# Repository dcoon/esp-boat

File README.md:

# ESP32 Multitool

ESP32 Multitool is an I/O board for ESP32 microcontroller based projects.  It is designed for IoT projects on a boat but can be used in automotive, RV, and home environments.  It is designed to be inexpensive, robust, energy efficient, and easy to use.  It supports firmware from multiple open source projects including ESPHome, ESPSense, and Platformio.

![[esp32-multitool.png]]

## Features

- 4x Analog Inputs
	- +0-30VDC
	- Measure voltage or resistance
- 4x Digital Inputs
- 4x PWM/Switch Outputs
	- Configurable voltage from VIN, +5V, and External
	- 1A current per channel
- CAN/N2K 
- 1-Wire
- I2C
	- Qwiic and Adafruit compatible I2C connector
- Power
	- +5 - 30VDC Input
	- OVP, RV, and ESD Protection
- Software Compatibility
	- ESPHome
	- ESPSense
	- Platformio

## Examples

TBD

### Tank Level Monitor
### Engine Monitor
### Fan Controller
### LED Dimmer

### More
- Refridgerator Controller
- Barometer & Lightning Detector

## Acknowledgements

### Sailorhat

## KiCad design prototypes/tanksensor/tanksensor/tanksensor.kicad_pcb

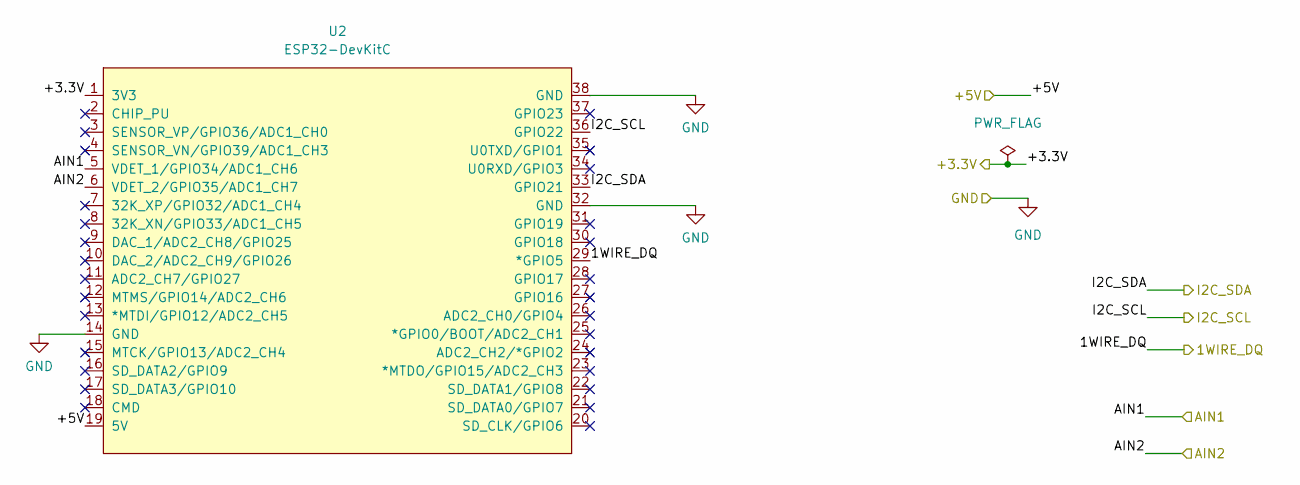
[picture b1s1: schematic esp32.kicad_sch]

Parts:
U2: ESP32-DevKitC; LCSC n/a

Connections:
+3.3V: U2.1 (3V3); also elsewhere on the board
/1WIRE_DQ: U2.29 (*GPIO5); also elsewhere on the board
/+5V: U2.19 (5V); also elsewhere on the board
/AIN1: U2.5 (VDET_1/GPIO34/ADC1_CH6); also elsewhere on the board
/AIN2: U2.6 (VDET_2/GPIO35/ADC1_CH7); also elsewhere on the board
/I2C_SCL: U2.36 (GPIO22); also elsewhere on the board
/I2C_SDA: U2.33 (GPIO21); also elsewhere on the board
GND: U2.14 (GND), U2.32 (GND), U2.38 (GND); also elsewhere on the board

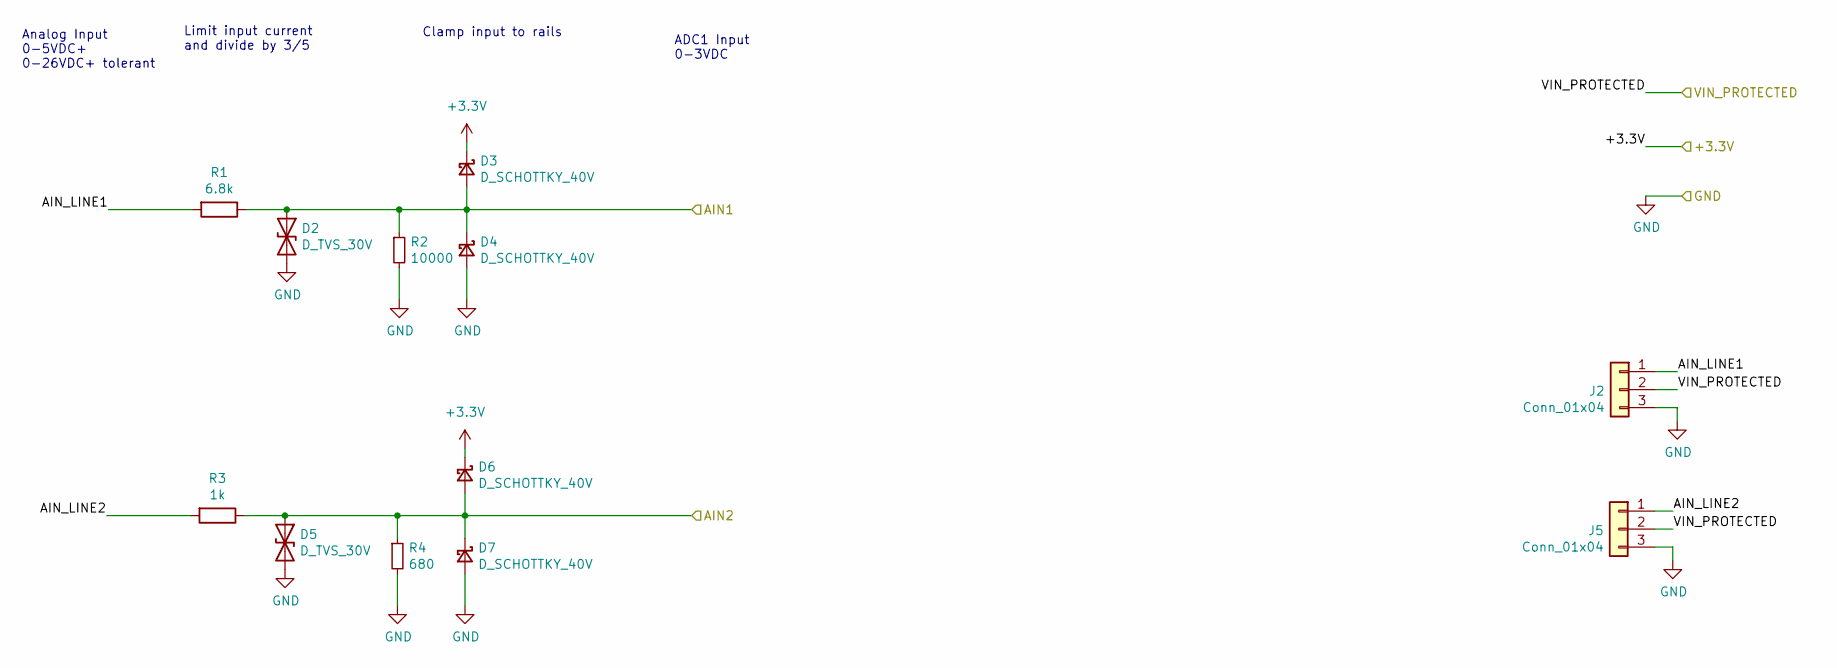
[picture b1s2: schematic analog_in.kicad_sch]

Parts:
D2, D5: D_TVS_30V; D_SOD-123F; Part SMFJ30CA; LCSC C511921
D3, D4, D6, D7: D_SCHOTTKY_40V; D_SMA; Part B5819W SL; LCSC C8598
J2, J5: Conn_01x04; Molex_KK-254_AE-6410-03A_1x03_P2.54mm_Vertical; Part C145961; LCSC C145961
R1: 6.8k; R_0805_2012Metric; Part 0603WAF1003T5E; LCSC C25803
R2: 10000; R_0805_2012Metric; Part 0603WAF1004T5E; LCSC C22935
R3: 1k; R_0805_2012Metric; Part 0603WAF1003T5E; LCSC C25803
R4: 680; R_0805_2012Metric; Part 0603WAF1004T5E; LCSC C22935

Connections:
+3.3V: D3.1 (K), D6.1 (K); also elsewhere on the board
/AIN1: D2.1 (A1), D3.2 (A), D4.1 (K), R1.1, R2.1; also elsewhere on the board
/AIN2: D5.1 (A1), D6.2 (A), D7.1 (K), R3.1, R4.1; also elsewhere on the board
/VIN_PROTECTED: J2.2, J5.2; also elsewhere on the board
/analog_in/AIN_LINE1: J2.1, R1.2
/analog_in/AIN_LINE2: J5.1, R3.2
GND: D2.2 (A2), D4.2 (A), D5.2 (A2), D7.2 (A), J2.3, J5.3, R2.2, R4.2; also elsewhere on the board

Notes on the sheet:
ADC1 Input 0-3VDC
Limit input current and divide by 3/5
Analog Input 0-5VDC+ 0-26VDC+ tolerant
Clamp input to rails

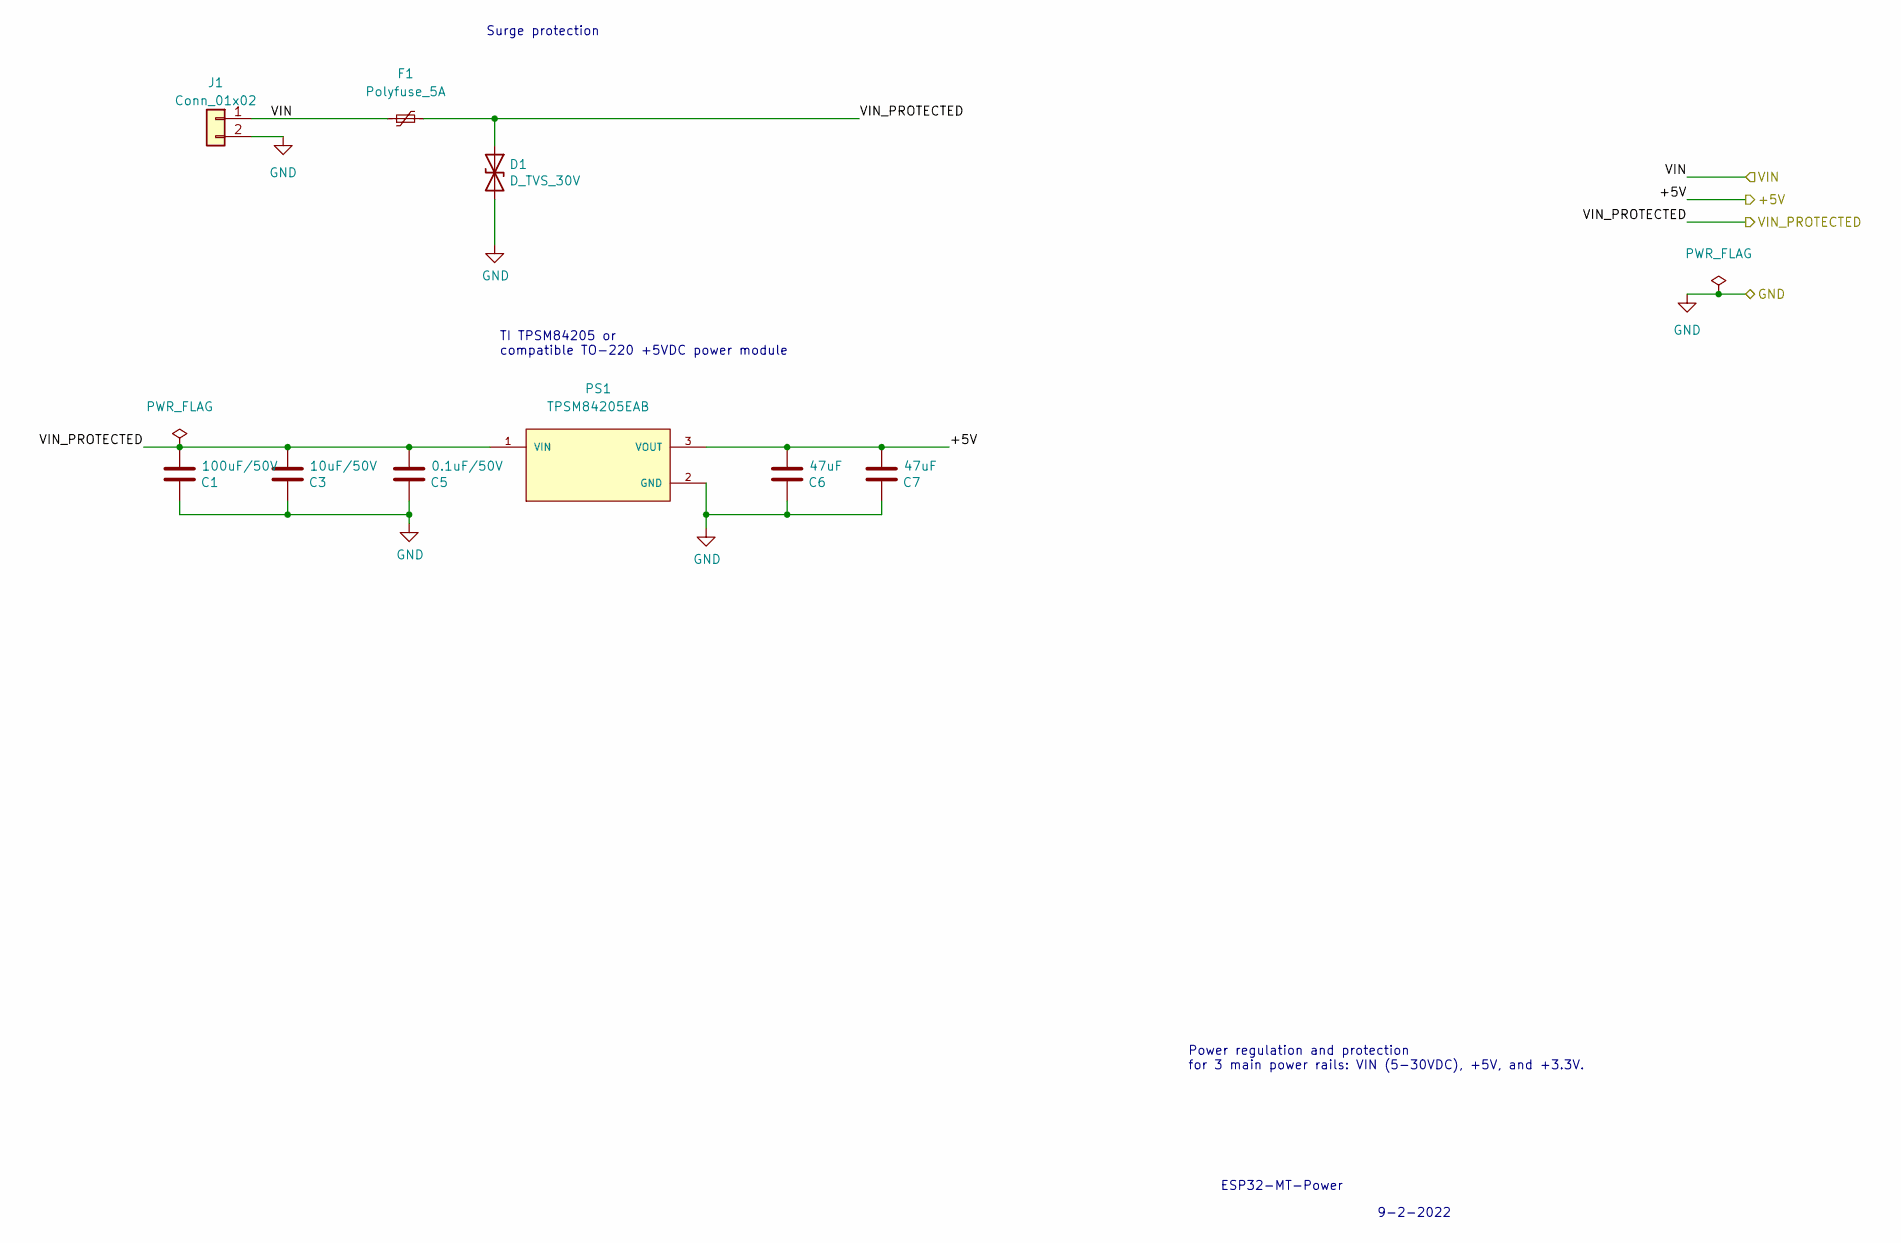
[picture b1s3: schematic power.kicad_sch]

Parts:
C1: 100uF/50V; C_0805_2012Metric; Part GRM21BR61H106KE43L; LCSC C440198
C3: 10uF/50V; C_0805_2012Metric; Part GRM21BR61H106KE43L; LCSC C440198
C5: 0.1uF/50V; C_0805_2012Metric; Part GRM21BR61H106KE43L; LCSC C440198
C6, C7: 47uF; C_0805_2012Metric; Part GRM21BR61H106KE43L; LCSC C440198
D1: D_TVS_30V; D_SOD-123F; Part SMFJ30CA; LCSC C511921
F1: Polyfuse_5A; Fuse_Bourns_MF-RG1000; Part JK30-200; LCSC C369104
J1: Conn_01x02; Molex_KK-254_AE-6410-02A_1x02_P2.54mm_Vertical; Part VH-2A; LCSC C16728
PS1: TPSM84205EAB; CONV_TPSM84205EAB

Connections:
/+5V: C6.1, C7.1, PS1.3 (VOUT); also elsewhere on the board
/VIN: F1.1, J1.1
/VIN_PROTECTED: C1.1, C3.1, C5.1, D1.1 (A1), F1.2, PS1.1 (VIN); also elsewhere on the board
GND: C1.2, C3.2, C5.2, C6.2, C7.2, D1.2 (A2), J1.2, PS1.2 (GND); also elsewhere on the board

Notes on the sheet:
Power regulation and protection for 3 main power rails: VIN (5-30VDC), +5V, and +3.3V.
9-2-2022
ESP32-MT-Power
TI TPSM84205 or compatible TO-220 +5VDC power module
Surge protection

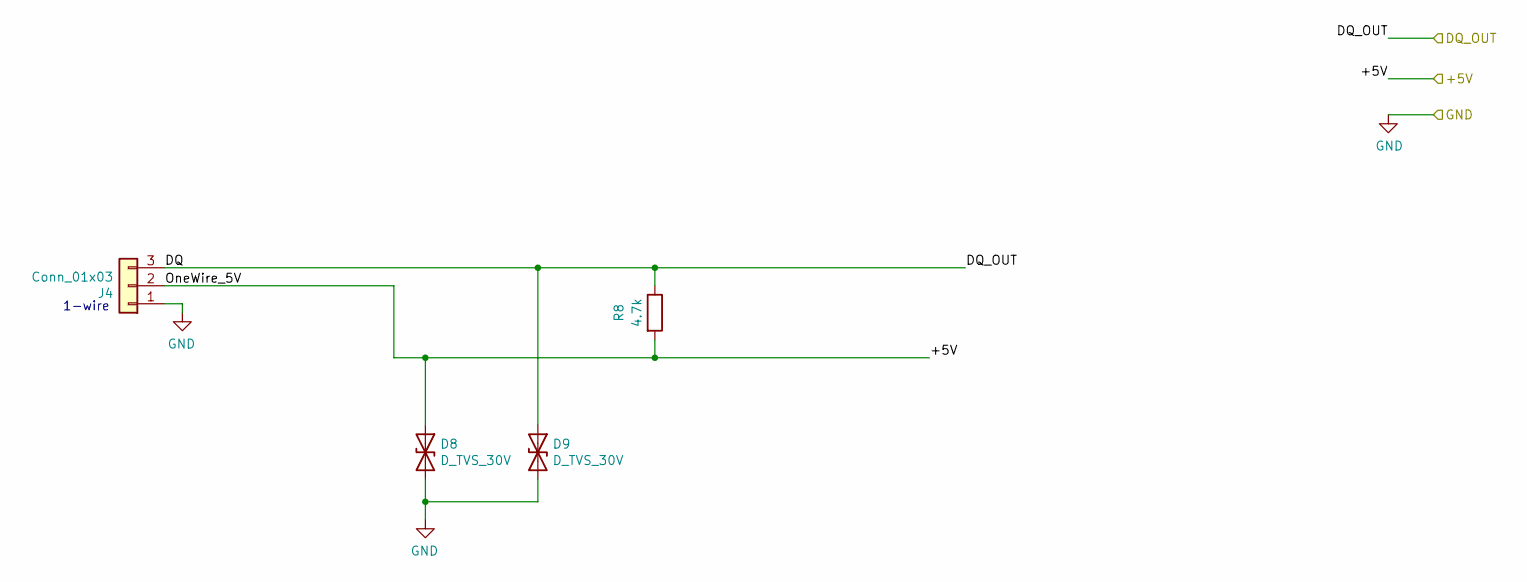
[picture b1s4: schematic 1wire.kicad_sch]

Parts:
D8, D9: D_TVS_30V; D_SOD-123F; Part SMFJ30CA; LCSC C511921
J4: Conn_01x03; Molex_KK-254_AE-6410-03A_1x03_P2.54mm_Vertical; Part C145960; LCSC C145960
R8: 4.7k; R_0805_2012Metric; Part 0603WAF4701T5E; LCSC C23162

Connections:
/1WIRE_DQ: D9.1 (A1), J4.3, R8.1; also elsewhere on the board
/+5V: D8.1 (A1), J4.2, R8.2; also elsewhere on the board
GND: D8.2 (A2), D9.2 (A2), J4.1; also elsewhere on the board

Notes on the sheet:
1-wire

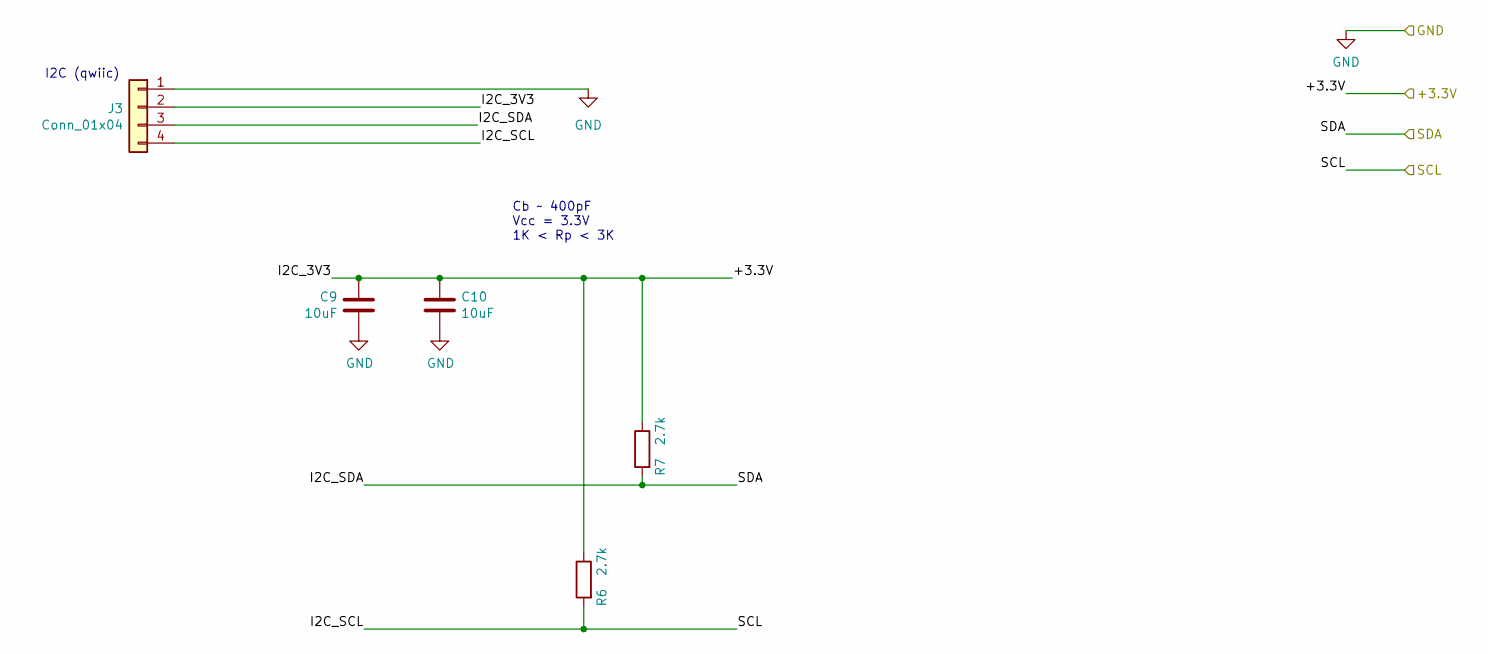
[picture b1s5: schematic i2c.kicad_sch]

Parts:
C9, C10: 10uF; C_0805_2012Metric; Part CL10A106KP8NNNC; LCSC C19702
J3: Conn_01x04; Molex_KK-254_AE-6410-04A_1x04_P2.54mm_Vertical; Part C145961; LCSC C145961
R6, R7: 2.7k; R_0805_2012Metric; Part 0603WAF2701T5E; LCSC C13167

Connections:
+3.3V: C9.1, C10.1, J3.2, R6.1, R7.1; also elsewhere on the board
/I2C_SCL: J3.4, R6.2; also elsewhere on the board
/I2C_SDA: J3.3, R7.2; also elsewhere on the board
GND: C9.2, C10.2, J3.1; also elsewhere on the board

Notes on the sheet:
Cb ~ 400pF Vcc = 3.3V 1K < Rp < 3K
I2C (qwiic)

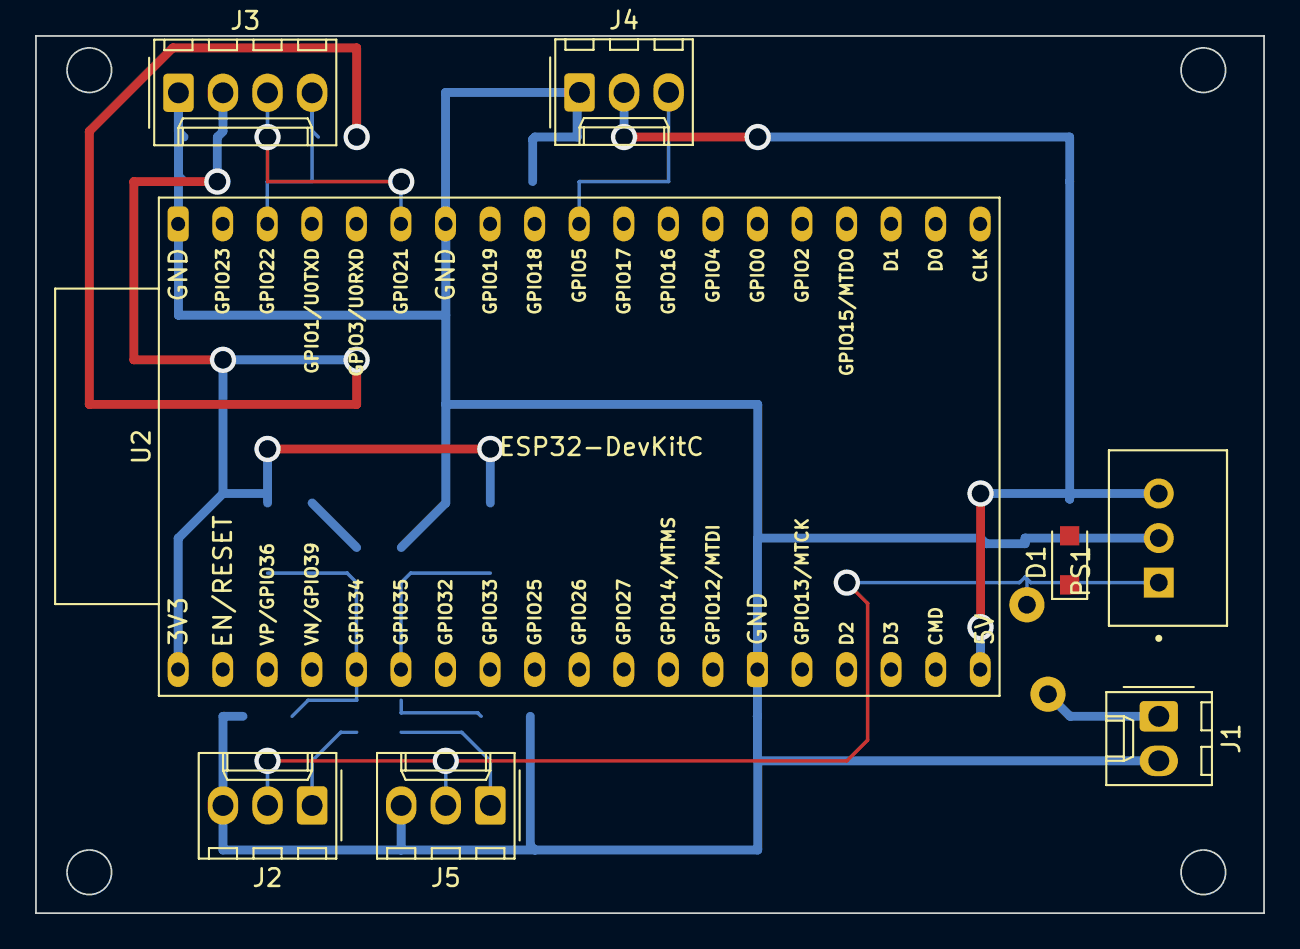
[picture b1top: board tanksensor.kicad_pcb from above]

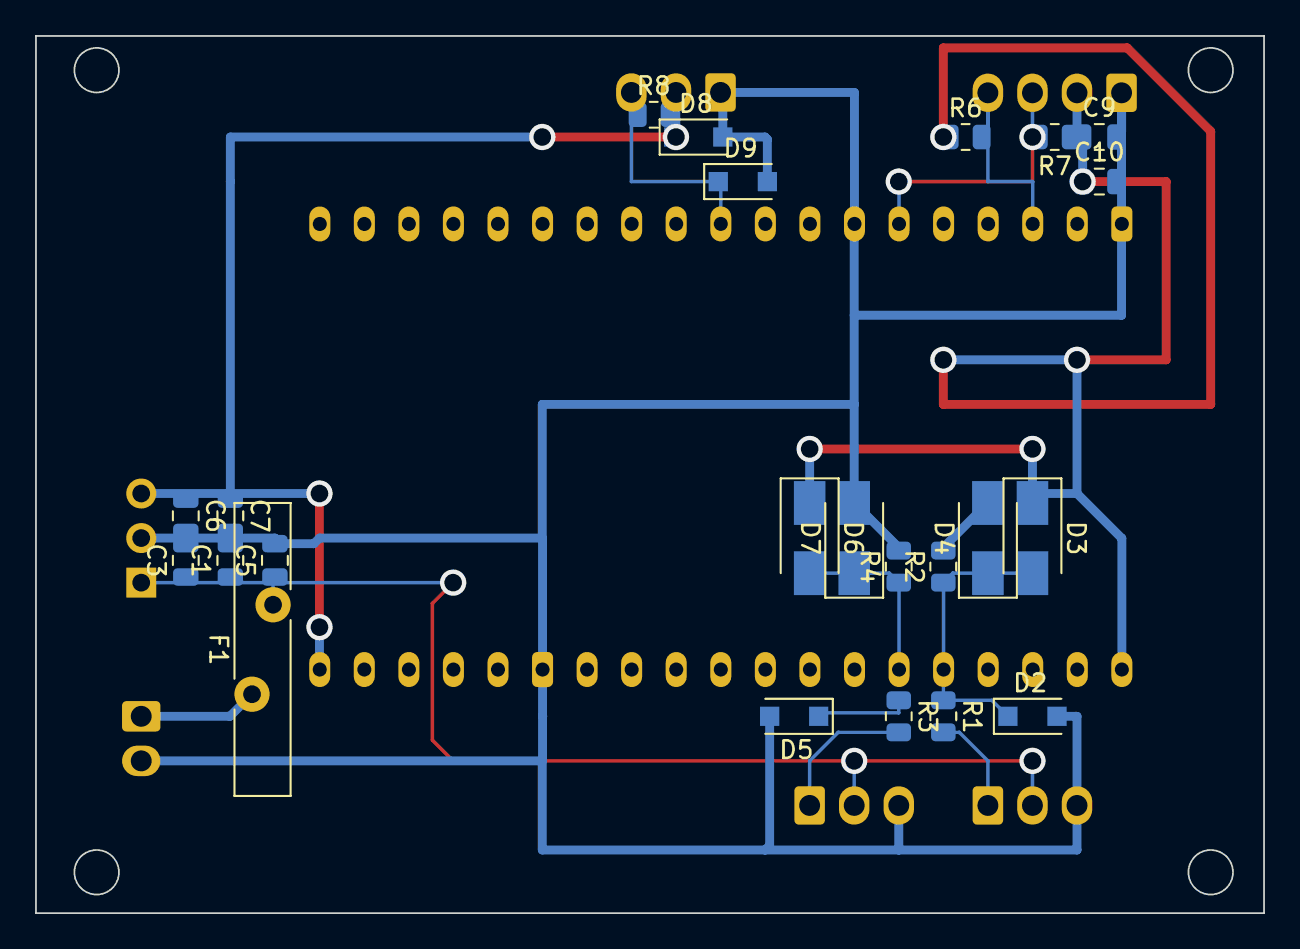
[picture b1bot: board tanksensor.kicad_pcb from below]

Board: 2 copper layers, 70.0 x 50.0 mm, 31 parts (23 on the bottom side), 12 nets.

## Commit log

2022-09-20 Created repository
2022-09-20 First pass at tank sensor proto
2022-09-22 Added zips and auto_saved_files to gitignore
2022-09-23 Rev of the tanksensor pcb and esphome config
